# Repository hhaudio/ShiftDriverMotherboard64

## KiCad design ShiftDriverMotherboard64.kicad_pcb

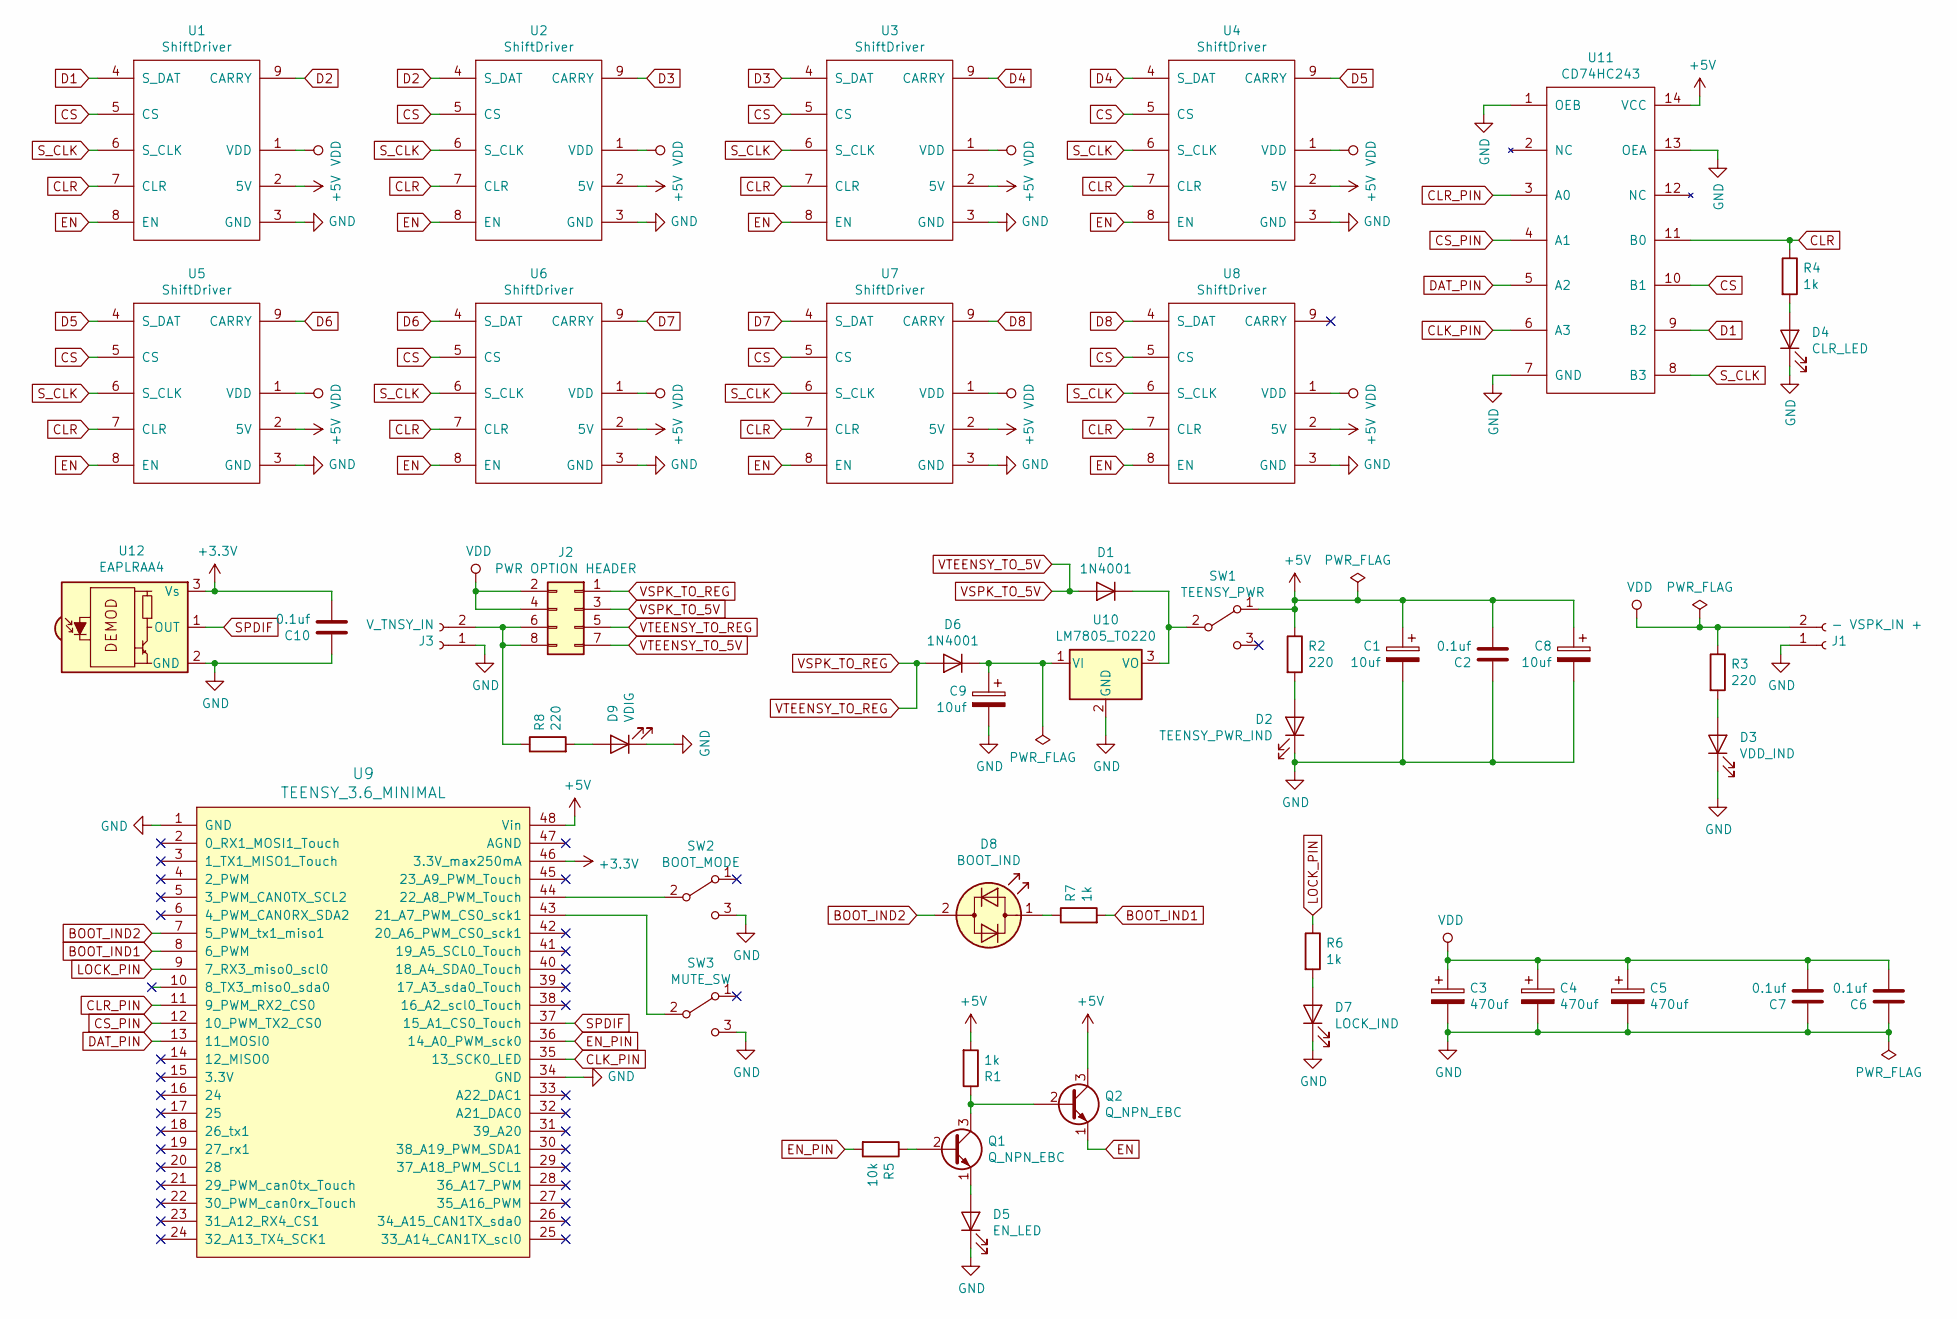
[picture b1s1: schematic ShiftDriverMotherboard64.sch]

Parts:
C1, C8, C9: 10uf; CP_Radial_D5.0mm_P2.00mm
C2, C6, C7, C10: 0.1uf; C_Disc_D3.0mm_W2.0mm_P2.50mm
C3, C4, C5: 470uf; CP_Radial_D10.0mm_P5.00mm
D1, D6: 1N4001; D_DO-41_SOD81_P7.62mm_Horizontal
D2: TEENSY_PWR_IND; LED_D5.0mm
D3: VDD_IND; LED_D5.0mm
D4: CLR_LED; LED_D5.0mm
D5: EN_LED; LED_D5.0mm
D7: LOCK_IND; LED_D5.0mm
D8: BOOT_IND; LED_D5.0mm
D9: VDIG; LED_D5.0mm
J1: - VSPK_IN +; ScrewTerm+Phoenix_30A_7.62mm_1x2
J2: PWR OPTION HEADER; PinHeader_2x04_P2.54mm_Vertical
J3: V_TNSY_IN; Phoenix_Stacked
Q1, Q2: Q_NPN_EBC; TO-92L_Inline_Wide
R1, R4, R6, R7: 1k; R_THT_P7.62
R2, R3, R8: 220; R_THT_P7.62
R5: 10k; R_THT_P7.62
SW1: TEENSY_PWR; Tayda_Slide_SPDT
SW2: BOOT_MODE; Tayda_Slide_SPDT
SW3: MUTE_SW; Tayda_Slide_SPDT
U1, U2, U3, U4, U5, U6, U7, U8: ShiftDriver; ShiftDriverV0.1
U9: TEENSY_3.6_MINIMAL; TEENSY_3.5_3.6_MINIMAL
U10: LM7805_TO220; TO-220-3_Horizontal_TabDown
U11: CD74HC243; DIP-14_W7.62mm_Socket
U12: EAPLRAA4

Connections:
+3V3: C10.2, U9.46 (3.3V_max250mA), U12.3 (Vs)
+5V: C1.1, C2.2, C8.1, Q2.3 (C), R1.2, R2.1, SW1.1 (A), U1.2 (5V), U2.2 (5V), U3.2 (5V), U4.2 (5V), U5.2 (5V), U6.2 (5V), U7.2 (5V), U8.2 (5V), U9.48 (Vin), U11.14 (VCC)
BOOT_IND1: R7.2, U9.8 (6_PWM)
BOOT_IND2: D8.2 (AK), U9.7 (5_PWM_tx1_miso1)
CLK_PIN: U9.35 (13_SCK0_LED), U11.6 (A3)
CLR: R4.1, U1.7 (CLR), U2.7 (CLR), U3.7 (CLR), U4.7 (CLR), U5.7 (CLR), U6.7 (CLR), U7.7 (CLR), U8.7 (CLR), U11.11 (B0)
CLR_PIN: U9.11 (9_PWM_RX2_CS0), U11.3 (A0)
CS: U1.5 (CS), U2.5 (CS), U3.5 (CS), U4.5 (CS), U5.5 (CS), U6.5 (CS), U7.5 (CS), U8.5 (CS), U11.10 (B1)
CS_PIN: U9.12 (10_PWM_TX2_CS0), U11.4 (A1)
D1: U1.4 (S_DAT), U11.9 (B2)
D2: U1.9 (CARRY), U2.4 (S_DAT)
D3: U2.9 (CARRY), U3.4 (S_DAT)
D4: U3.9 (CARRY), U4.4 (S_DAT)
D5: U4.9 (CARRY), U5.4 (S_DAT)
D6: U5.9 (CARRY), U6.4 (S_DAT)
D7: U6.9 (CARRY), U7.4 (S_DAT)
D8: U7.9 (CARRY), U8.4 (S_DAT)
DAT_PIN: U9.13 (11_MOSI0), U11.5 (A2)
EN: Q2.1 (E), U1.8 (EN), U2.8 (EN), U3.8 (EN), U4.8 (EN), U5.8 (EN), U6.8 (EN), U7.8 (EN), U8.8 (EN)
EN_PIN: R5.2, U9.36 (14_A0_PWM_sck0)
GND: C1.2, C2.1, C3.2, C4.2, C5.2, C6.1, C7.1, C8.2, C9.2, C10.1, D2.1 (K), D3.1 (K), D4.1 (K), D5.1 (K), D7.1 (K), D9.1 (K), J1.1, J3.1, SW2.3 (C), SW3.3 (C), U1.3 (GND), U2.3 (GND), U3.3 (GND), U4.3 (GND), U5.3 (GND), U6.3 (GND), U7.3 (GND), U8.3 (GND), U9.1 (GND), U9.34 (GND), U10.2 (GND), U11.1 (OEB), U11.7 (GND), U11.13 (OEA), U12.2 (GND)
LOCK_PIN: R6.1, U9.9 (7_RX3_miso0_scl0)
unnamed: C9.1, D6.1 (K), U10.1 (VI)
unnamed: D1.1 (K), SW1.2 (B), U10.3 (VO)
unnamed: D2.2 (A), R2.2
unnamed: D3.2 (A), R3.2
unnamed: D4.2 (A), R4.2
unnamed: D5.2 (A), Q1.1 (E)
unnamed: D7.2 (A), R6.2
unnamed: D8.1 (KA), R7.1
unnamed: D9.2 (A), R8.2
unnamed: J2.6, J2.8, J3.2, R8.1
unnamed: Q1.2 (B), R5.1
unnamed: Q1.3 (C), Q2.2 (B), R1.1
unnamed: SW2.2 (B), U9.44 (22_A8_PWM_Touch)
unnamed: SW3.2 (B), U9.43 (21_A7_PWM_CS0_sck1)
SPDIF: U9.37 (15_A1_CS0_Touch), U12.1 (OUT)
S_CLK: U1.6 (S_CLK), U2.6 (S_CLK), U3.6 (S_CLK), U4.6 (S_CLK), U5.6 (S_CLK), U6.6 (S_CLK), U7.6 (S_CLK), U8.6 (S_CLK), U11.8 (B3)
VDD: C3.1, C4.1, C5.1, C6.2, C7.2, J1.2, J2.2, J2.4, R3.1, U1.1 (VDD), U2.1 (VDD), U3.1 (VDD), U4.1 (VDD), U5.1 (VDD), U6.1 (VDD), U7.1 (VDD), U8.1 (VDD)
VSPK_TO_5V: D1.2 (A), J2.3, J2.7
VSPK_TO_REG: D6.2 (A), J2.1, J2.5

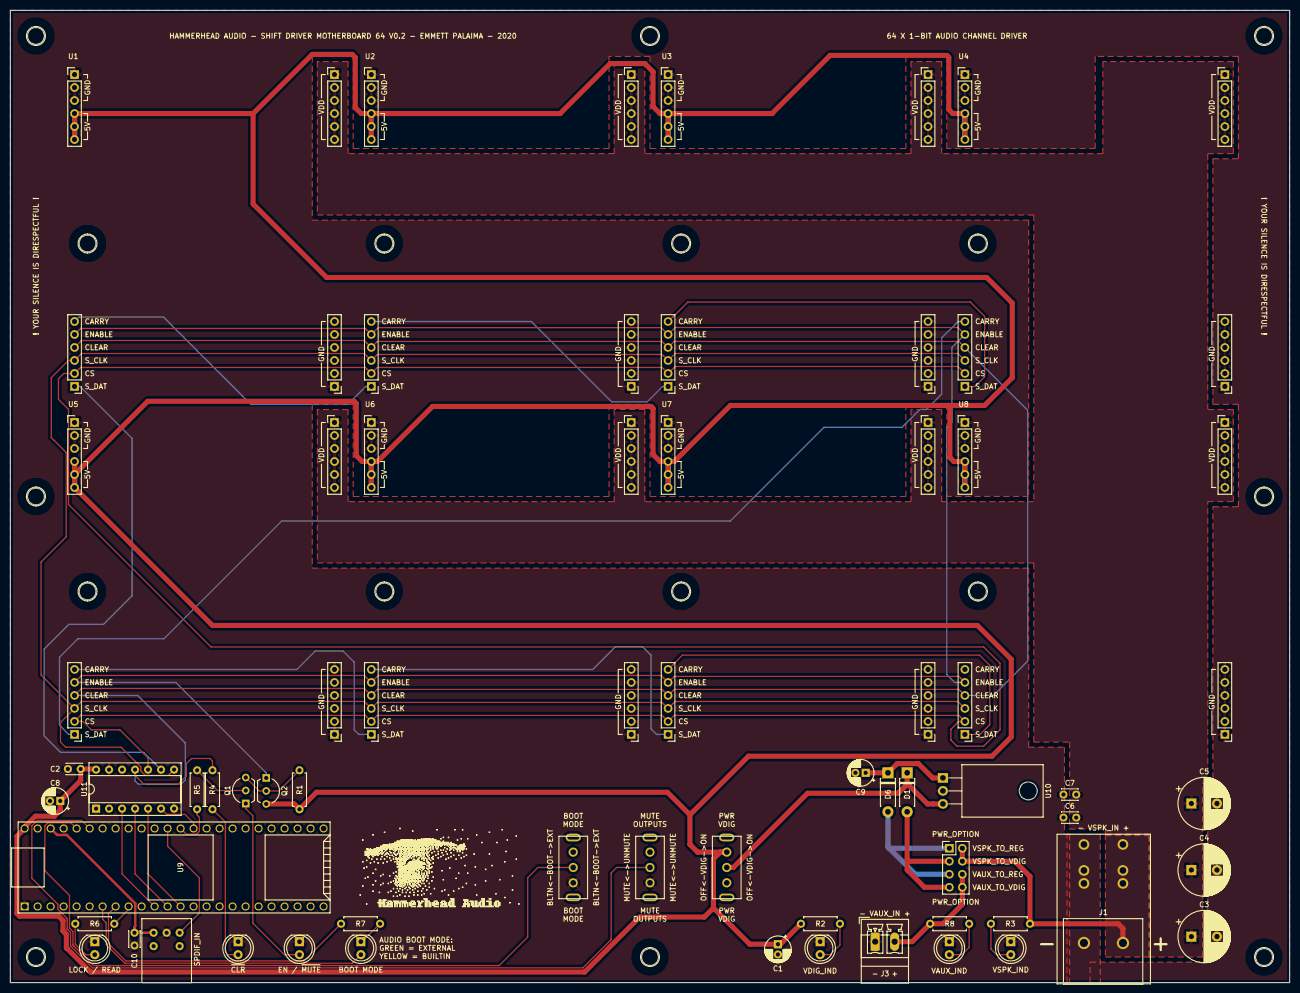
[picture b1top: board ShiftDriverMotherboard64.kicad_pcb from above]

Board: 2 copper layers, 250.0 x 190.0 mm, 58 parts (1 on the bottom side), 41 nets.

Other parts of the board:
H3, H3#2, H3#3, H3#4, H3#5, H3#6, H3#7, H3#8: M3/#4-40; M3_MOUNT
HH_LOGO_32x16, HH_LOGO_32x16#2, HH_LOGO_32x16#3: HH_LOGO_32x16

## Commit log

2020-05-18 started scheamtic
2020-06-14 finished scheamtic
2020-06-19 first crack at layout, gonna try laying traces soon
2020-06-19 start on power planes
2020-06-19 finished power plane
2020-06-19 finished ground plane
2020-06-20 finished first draft of layout
2020-06-20 finished layout tweaks, made gerbers
2020-06-20 ready for printing
2020-07-02 fixed shift driver footprint and resized board
2020-07-03 finished new layout
2020-07-03 final tweaks, made gerbers
